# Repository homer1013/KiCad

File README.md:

# KiCad
 PCB projects

 All PCB development saved here

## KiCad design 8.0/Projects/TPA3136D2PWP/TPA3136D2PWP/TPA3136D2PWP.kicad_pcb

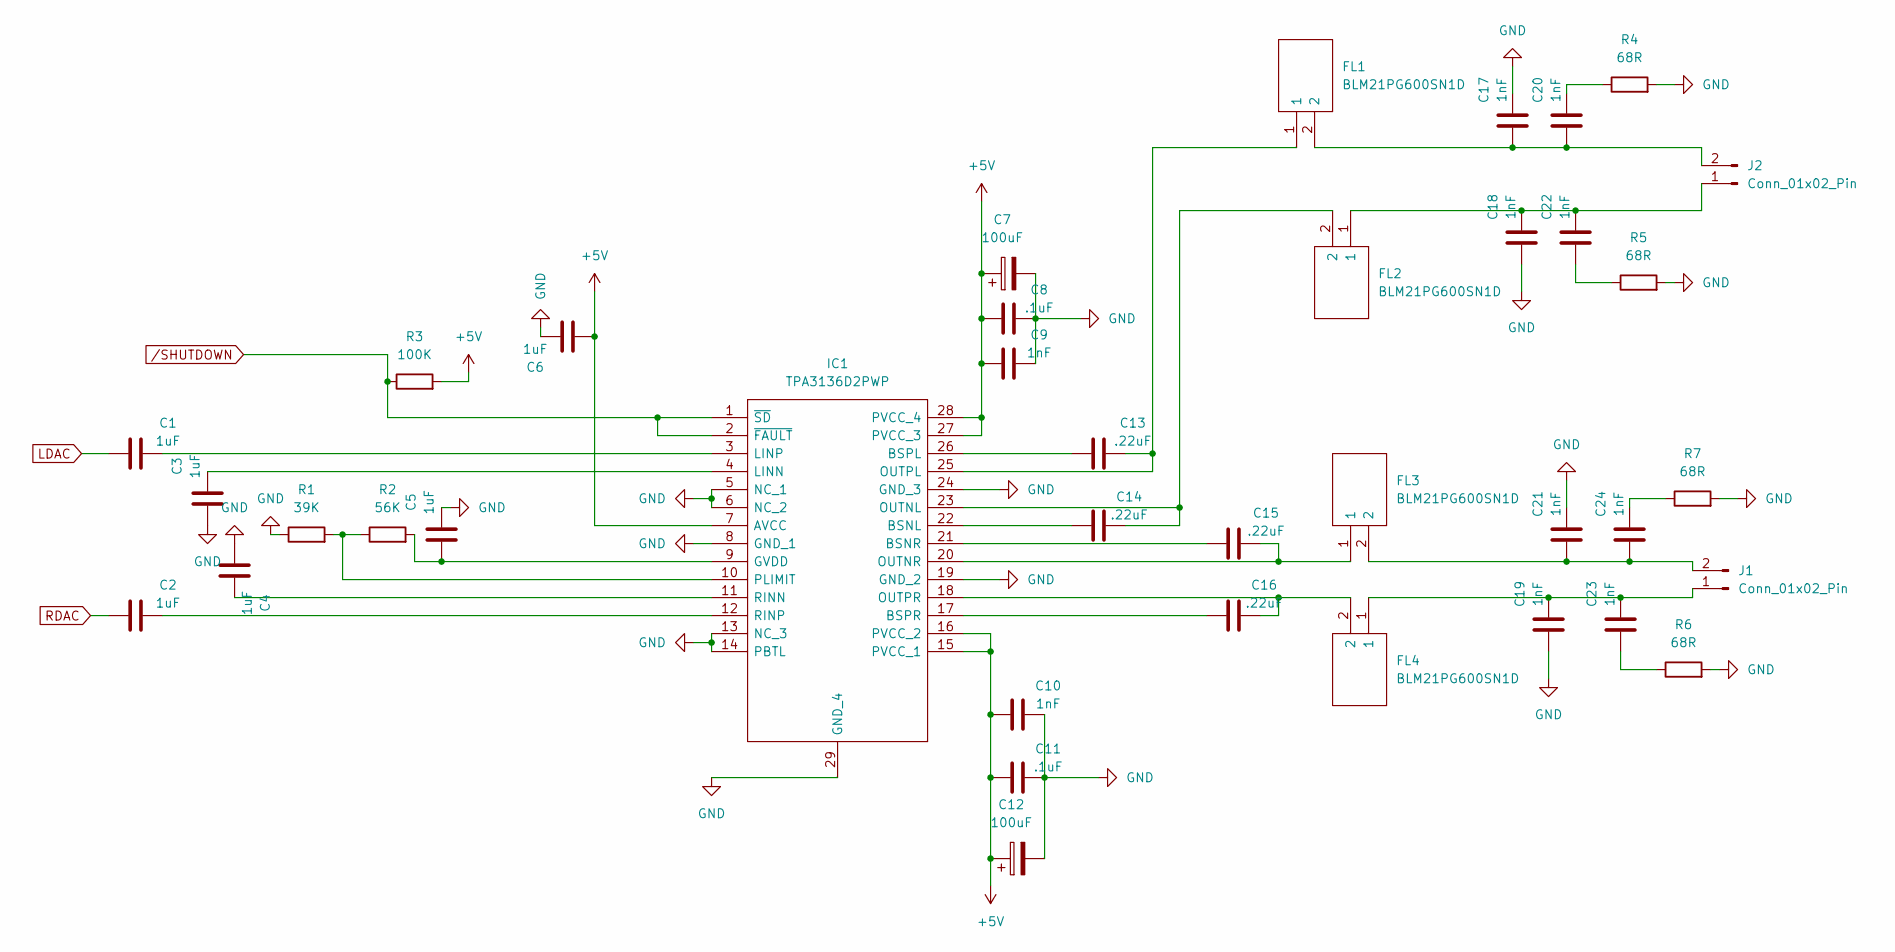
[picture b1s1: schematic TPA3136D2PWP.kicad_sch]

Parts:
C1, C2, C3, C4, C5, C6: 1uF; C_0805_2012Metric_Pad1.18x1.45mm_HandSolder
C7, C12: 100uF; C_0805_2012Metric_Pad1.18x1.45mm_HandSolder
C8, C11: .1uF; C_0805_2012Metric_Pad1.18x1.45mm_HandSolder
C9, C10, C17, C18, C19, C20, C21, C22, C23, C24: 1nF; C_0805_2012Metric_Pad1.18x1.45mm_HandSolder
C13, C14, C15, C16: .22uF; C_0805_2012Metric_Pad1.18x1.45mm_HandSolder
FL1, FL2, FL3, FL4: BLM21PG600SN1D; BLM21AG102BH1J; Mouser Part Number 81-BLM21P600S
IC1: TPA3136D2PWP; SOP65P640X120-29N; Mouser Part Number 595-TPA3136D2PWP
J1, J2: Conn_01x02_Pin; PinHeader_1x02_P2.54mm_Vertical
R1: 39K; R_0805_2012Metric_Pad1.20x1.40mm_HandSolder
R2: 56K; R_0805_2012Metric_Pad1.20x1.40mm_HandSolder
R3: 100K; R_0805_2012Metric_Pad1.20x1.40mm_HandSolder
R4, R5, R6, R7: 68R; R_0805_2012Metric_Pad1.20x1.40mm_HandSolder

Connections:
+5V: C6.2, C7.1, C8.2, C9.2, C10.2, C11.2, C12.1, IC1.7 (AVCC), IC1.15 (PVCC_1), IC1.16 (PVCC_2), IC1.27 (PVCC_3), IC1.28 (PVCC_4), R3.2
GND: C3.2, C4.2, C5.1, C6.1, C7.2, C8.1, C9.1, C10.1, C11.1, C12.2, C17.1, C18.2, C19.2, C21.1, IC1.5 (NC_1), IC1.6 (NC_2), IC1.8 (GND_1), IC1.13 (NC_3), IC1.14 (PBTL), IC1.19 (GND_2), IC1.24 (GND_3), IC1.29 (GND_4), R1.1, R4.2, R5.2, R6.2, R7.2
LDAC: C1.2
unnamed: C20.1, R4.1
unnamed: C22.2, R5.1
unnamed: C23.2, R6.1
unnamed: C24.1, R7.1
unnamed: C14.2, IC1.22 (BSNL)
unnamed: C15.2, IC1.21 (BSNR)
unnamed: C13.2, IC1.26 (BSPL)
unnamed: C16.2, IC1.17 (BSPR)
unnamed: C5.2, IC1.9 (GVDD), R2.2
unnamed: C3.1, IC1.4 (LINN)
unnamed: C1.1, IC1.3 (LINP)
unnamed: C14.1, FL2.2, IC1.23 (OUTNL)
unnamed: C15.1, FL3.1, IC1.20 (OUTNR)
unnamed: C13.1, FL1.1, IC1.25 (OUTPL)
unnamed: C16.1, FL4.2, IC1.18 (OUTPR)
unnamed: IC1.10 (PLIMIT), R1.2, R2.1
unnamed: C4.1, IC1.11 (RINN)
unnamed: C2.1, IC1.12 (RINP)
unnamed: C19.1, C23.1, FL4.1, J1.1
unnamed: C21.2, C24.2, FL3.2, J1.2
unnamed: C18.1, C22.1, FL2.1, J2.1
unnamed: C17.2, C20.2, FL1.2, J2.2
RDAC: C2.2
/SHUTDOWN: IC1.1 (~SD), IC1.2 (~FAULT), R3.1

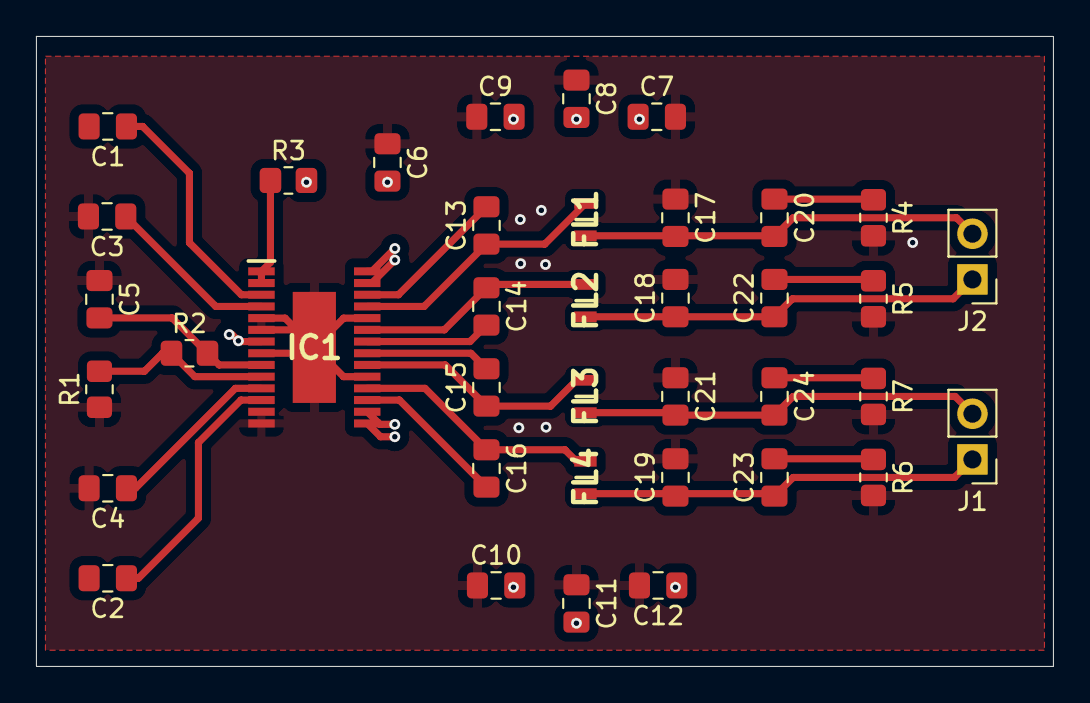
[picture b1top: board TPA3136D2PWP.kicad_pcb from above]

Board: 4 copper layers, 56.5 x 35.0 mm, 38 parts (0 on the bottom side), 25 nets.

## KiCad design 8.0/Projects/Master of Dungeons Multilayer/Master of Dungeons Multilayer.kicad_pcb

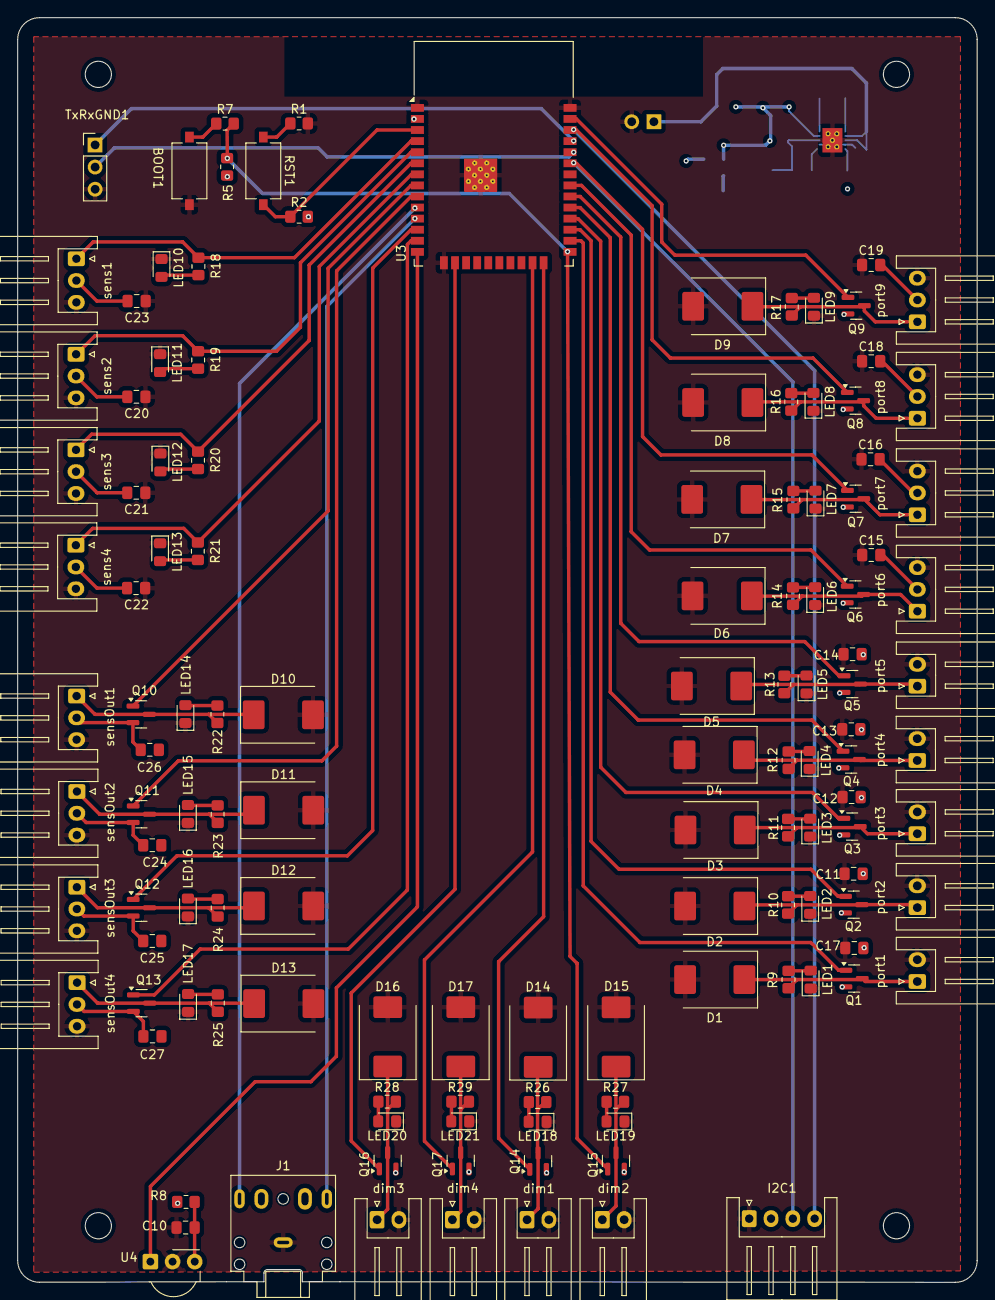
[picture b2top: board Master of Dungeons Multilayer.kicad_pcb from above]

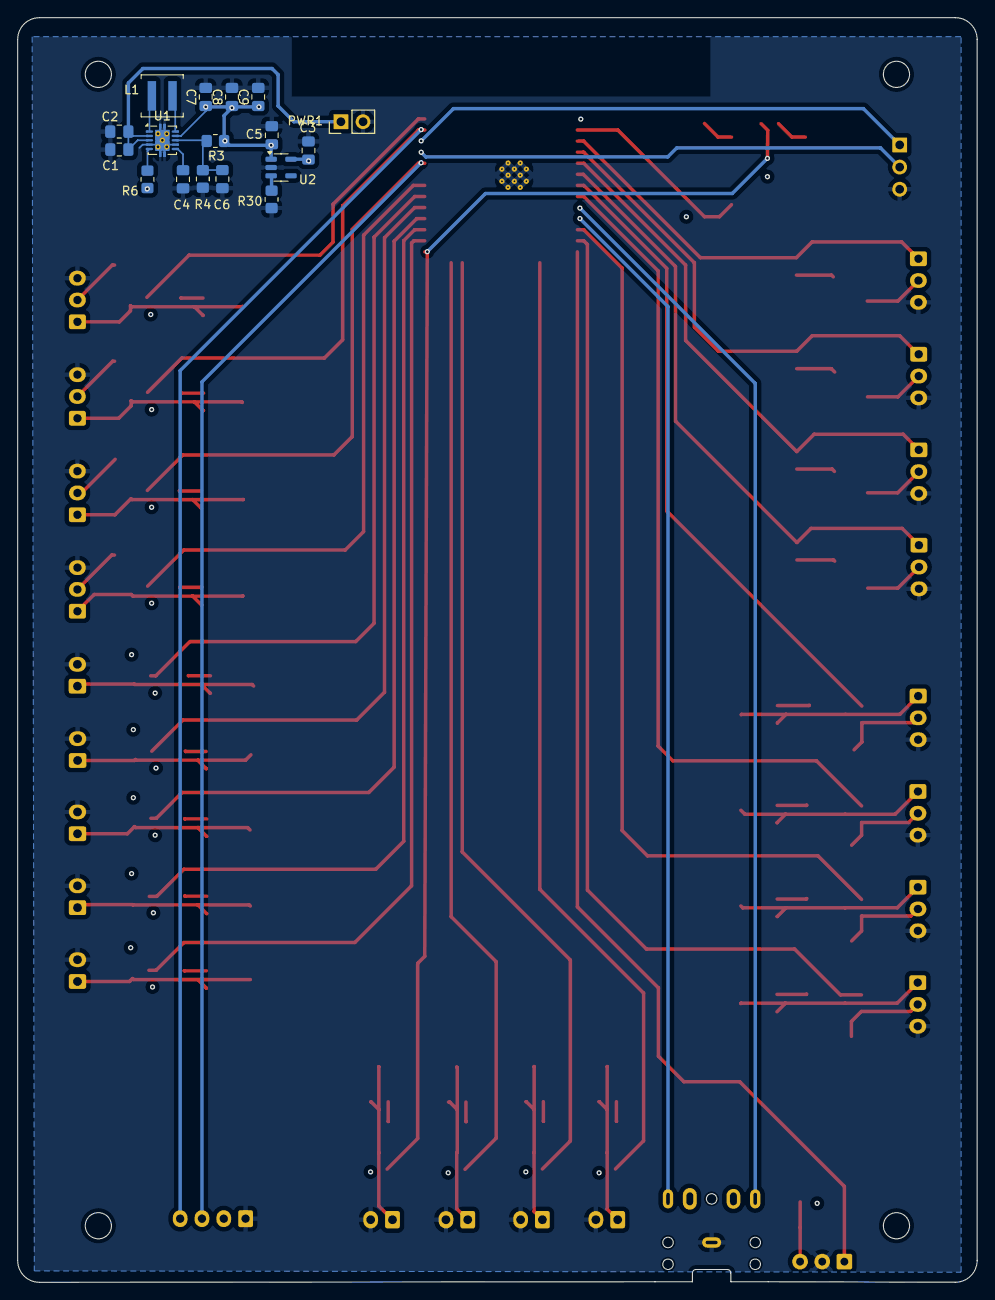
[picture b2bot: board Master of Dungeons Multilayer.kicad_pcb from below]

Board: 4 copper layers, 110.0 x 145.0 mm, 144 parts (17 on the bottom side), 78 nets.

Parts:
BOOT1: SW_Push; SW_Tactile_SPST_NO_Straight_CK_PTS636Sx25SMTRLFS
C1, C2: 10uF; C_0805_2012Metric_Pad1.18x1.45mm_HandSolder
C3, C5: 1uF; C_0805_2012Metric_Pad1.18x1.45mm_HandSolder
C4: .1uF; C_0805_2012Metric_Pad1.18x1.45mm_HandSolder
C6: 10pF; C_0805_2012Metric_Pad1.18x1.45mm_HandSolder
C7, C8, C9: 22uF; C_0805_2012Metric_Pad1.18x1.45mm_HandSolder
C10, C11, C12, C13, C14, C15, C16, C17, C18, C19: 100nF; C_0805_2012Metric_Pad1.18x1.45mm_HandSolder
C20, C21, C22, C23, C24, C25, C26, C27: C; C_0805_2012Metric_Pad1.18x1.45mm_HandSolder
D1, D2, D3, D4, D5, D6, D7, D8, D9, D10, D11, D12, D13, D14, D15, D16, D17: B340; D_SMC
I2C1: Conn_01x04_Pin; JST_XH_S4B-XH-A_1x04_P2.50mm_Horizontal
J1: AudioPlug3; Jack_3.5mm_CUI_SJ1-3525N_Horizontal
L1: L; L_Coilcraft_XAL4020-XXX
LED1, LED2, LED3, LED4, LED5, LED6, LED7, LED8, LED9, LED10, LED11, LED12, LED13: GREEN_0805; LED_0805_2012Metric_Pad1.15x1.40mm_HandSolder
LED14, LED15, LED16, LED17, LED18, LED19, LED20, LED21: LED; LED_0805_2012Metric_Pad1.15x1.40mm_HandSolder
PWR1: Conn_01x02_Pin; PinHeader_1x02_P2.54mm_Vertical
Q1, Q2, Q3, Q4, Q5, Q6, Q7, Q8, Q9, Q10, Q11, Q12, Q13, Q14, Q15, Q16, Q17: IRLML6244; SOT-23
R1, R7, R8: 470R; R_0805_2012Metric_Pad1.20x1.40mm_HandSolder
R2, R5, R9, R10, R11, R12, R13, R14, R15, R16, R17, R30: 12K; R_0805_2012Metric_Pad1.20x1.40mm_HandSolder
R3, R6: 1M; R_0805_2012Metric_Pad1.20x1.40mm_HandSolder
R4: 111K; R_0805_2012Metric_Pad1.20x1.40mm_HandSolder
R18, R19, R20, R21, R22, R23, R24, R25, R26, R27, R28, R29: R; R_0805_2012Metric_Pad1.20x1.40mm_HandSolder
RST1: SW_Push; SW_Tactile_SPST_NO_Straight_CK_PTS636Sx25SMTRLFS
TxRxGND1: Conn_01x03_Pin; PinHeader_1x03_P2.54mm_Vertical
U1: TPS63060; Texas_DSC0010J_ThermalVias
U2: AP2127K-3.3; SOT-23-5
U3: ESP32-WROOM-32E; ESP32-WROOM-32D
U4: TSOP45xx; Vishay_MOLD-3Pin
dim1, dim2, dim3, dim4: Conn_01x02_Pin; JST_XH_S2B-XH-A_1x02_P2.50mm_Horizontal
port1, port2, port3, port4, port5: JST_XH_2POS; JST_XH_S2B-XH-A_1x02_P2.50mm_Horizontal
port6, port7, port8, port9: JST_XH_3POS; JST_XH_S3B-XH-A_1x03_P2.50mm_Horizontal
sens1, sens2, sens3, sens4: Conn_01x03_Pin; JST_XH_S3B-XH-A_1x03_P2.50mm_Horizontal
sensOut1, sensOut2, sensOut3, sensOut4: Conn_01x03_Pin; JST_XH_S3B-XH-A_1x03_P2.50mm_Horizontal

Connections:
+3.3V: C3.1, R2.2, R5.1, U2.5 (VOUT), U3.2 (VDD)
+5V: C5.1, C7.1, C8.1, C9.1, C11.2, C12.2, C13.2, C14.2, C15.2, C16.2, C17.2, C18.2, C19.2, C20.1, C21.1, C22.1, C23.1, C24.2, C25.2, C26.2, C27.2, I2C1.2, Q1.2 (S), Q2.2 (S), Q3.2 (S), Q4.2 (S), Q5.2 (S), Q6.2 (S), Q7.2 (S), Q8.2 (S), Q9.2 (S), Q10.2 (S), Q11.2 (S), Q12.2 (S), Q13.2 (S), Q14.2 (S), Q15.2 (S), Q16.2 (S), Q17.2 (S), R3.2, R6.2, R8.2, U1.9 (VOUT), U2.1 (VIN), port6.2, port7.2, port8.2, port9.2, sens1.2, sens2.2, sens3.2, sens4.2, sensOut1.2, sensOut2.2, sensOut3.2, sensOut4.2
GND: BOOT1.2, C1.1, C2.2, C3.2, C4.2, C5.2, C6.2, C7.2, C8.2, C9.2, C10.1, C11.1, C12.1, C13.1, C14.1, C15.1, C16.1, C17.1, C18.1, C19.1, C20.2, C21.2, C22.2, C23.2, D1.2 (A), D2.2 (A), D3.2 (A), D4.2 (A), D5.2 (A), D6.2 (A), D7.2 (A), D8.2 (A), D9.2 (A), D10.2 (A), D11.2 (A), D12.2 (A), D13.2 (A), D14.2 (A), D15.2 (A), D16.2 (A), D17.2 (A), I2C1.1, J1.S, LED1.1 (K), LED2.1 (K), LED3.1 (K), LED4.1 (K), LED5.1 (K), LED6.1 (K), LED7.1 (K), LED8.1 (K), LED9.1 (K), LED10.1 (K), LED11.1 (K), LED12.1 (K), LED13.1 (K), LED14.1 (K), LED15.1 (K), LED16.1 (K), LED17.1 (K), LED18.1 (K), LED19.1 (K), LED20.1 (K), LED21.1 (K), PWR1.2, R1.2, R4.1, R30.1, TxRxGND1.3, U1.4 (PS/SYNC), U1.7 (GND), U1.11 (PGND), U2.2 (GND), U3.1 (GND), U3.15 (GND), U3.38 (GND), U3.39 (GND), U4.2 (GND), dim1.2, dim2.2, dim3.2, dim4.2, port1.2, port2.2, port3.2, port4.2, port5.2, port6.3, port7.3, port8.3, port9.3, sens1.3, sens2.3, sens3.3, sens4.3, sensOut1.3, sensOut2.3, sensOut3.3, sensOut4.3
unnamed: BOOT1.1, R7.1
unnamed: D1.1 (K), Q1.3 (D), R9.1, port1.1
unnamed: D2.1 (K), Q2.3 (D), R10.1, port2.1
unnamed: D3.1 (K), Q3.3 (D), R11.1, port3.1
unnamed: D4.1 (K), Q4.3 (D), R12.1, port4.1
unnamed: D5.1 (K), Q5.3 (D), R13.1, port5.1
unnamed: D6.1 (K), Q6.3 (D), R14.1, port6.1
unnamed: D7.1 (K), Q7.3 (D), R15.1, port7.1
unnamed: D8.1 (K), Q8.3 (D), R16.1, port8.1
unnamed: D9.1 (K), Q9.3 (D), R17.1, port9.1
unnamed: D10.1 (K), Q10.3 (D), R22.2, sensOut1.1
unnamed: D11.1 (K), Q11.3 (D), R23.2, sensOut2.1
unnamed: D12.1 (K), Q12.3 (D), R24.2, sensOut3.1
unnamed: D13.1 (K), Q13.3 (D), R25.2, sensOut4.1
unnamed: D14.1 (K), Q14.3 (D), R26.2, dim1.1
unnamed: D15.1 (K), Q15.3 (D), R27.2, dim2.1
unnamed: D16.1 (K), Q16.3 (D), R28.2, dim3.1
unnamed: D17.1 (K), Q17.3 (D), R29.2, dim4.1
unnamed: LED1.2 (A), R9.2
unnamed: LED2.2 (A), R10.2
unnamed: LED3.2 (A), R11.2
unnamed: LED4.2 (A), R12.2
unnamed: LED5.2 (A), R13.2
unnamed: LED6.2 (A), R14.2
unnamed: LED7.2 (A), R15.2
unnamed: LED8.2 (A), R16.2
unnamed: LED9.2 (A), R17.2
unnamed: LED10.2 (A), R18.1
unnamed: LED11.2 (A), R19.1
unnamed: LED12.2 (A), R20.1
unnamed: LED13.2 (A), R21.1
unnamed: LED14.2 (A), R22.1
unnamed: LED15.2 (A), R23.1
unnamed: LED16.2 (A), R24.1
unnamed: LED17.2 (A), R25.1
unnamed: LED18.2 (A), R26.1
unnamed: LED19.2 (A), R27.1
unnamed: LED20.2 (A), R28.1
unnamed: LED21.2 (A), R29.1
unnamed: C1.2, C2.1, PWR1.1, U1.2 (VIN), U1.3 (EN)
unnamed: R1.1, RST1.1
unnamed: TxRxGND1.1, U3.35 (TXD0/IO1)
unnamed: TxRxGND1.2, U3.34 (RXD0/IO3)
unnamed: C6.1, R3.1, R4.2, U1.8 (FB)
unnamed: L1.2, U1.1 (L1)
unnamed: L1.1, U1.10 (L2)
unnamed: R6.1, U1.5 (PG)
unnamed: C4.1, U1.6 (VAUX)
unnamed: R30.2, U2.3 (EN)
unnamed: R2.1, RST1.2, U3.3 (EN)
unnamed: U3.14 (IO12), U4.1 (OUT)
unnamed: J1.R, U3.10 (IO25)
unnamed: J1.T, U3.11 (IO26)
unnamed: C10.2, R8.1, U4.3 (Vs)
dim1: Q16.1 (G), U3.16 (IO13)
dim2: Q17.1 (G), U3.23 (IO15)
dim3: Q14.1 (G), U3.24 (IO2)
dim4: Q15.1 (G), R5.2, R7.2, U3.25 (IO0)
port1: Q1.1 (G), U3.26 (IO4)
port2: Q2.1 (G), U3.27 (IO16)
port3: Q3.1 (G), U3.28 (IO17)
port4: Q4.1 (G), U3.29 (IO5)
port5: Q5.1 (G), U3.30 (IO18)
port6: Q6.1 (G), U3.31 (IO19)
port7: I2C1.3, Q7.1 (G), U3.33 (IO21)
port8: I2C1.4, Q8.1 (G), U3.36 (IO22)
port9: Q9.1 (G), U3.37 (IO23)
sens1: R18.2, U3.4 (SENSOR_VP), sens1.1
sens2: R19.2, U3.5 (SENSOR_VN), sens2.1
sens3: R20.2, U3.6 (IO34), sens3.1
sens4: R21.2, U3.7 (IO35), sens4.1
sensOut1: Q10.1 (G), U3.8 (IO32)
sensOut2: Q11.1 (G), U3.9 (IO33)
sensOut3: Q12.1 (G), U3.12 (IO27)
sensOut4: Q13.1 (G), U3.13 (IO14)

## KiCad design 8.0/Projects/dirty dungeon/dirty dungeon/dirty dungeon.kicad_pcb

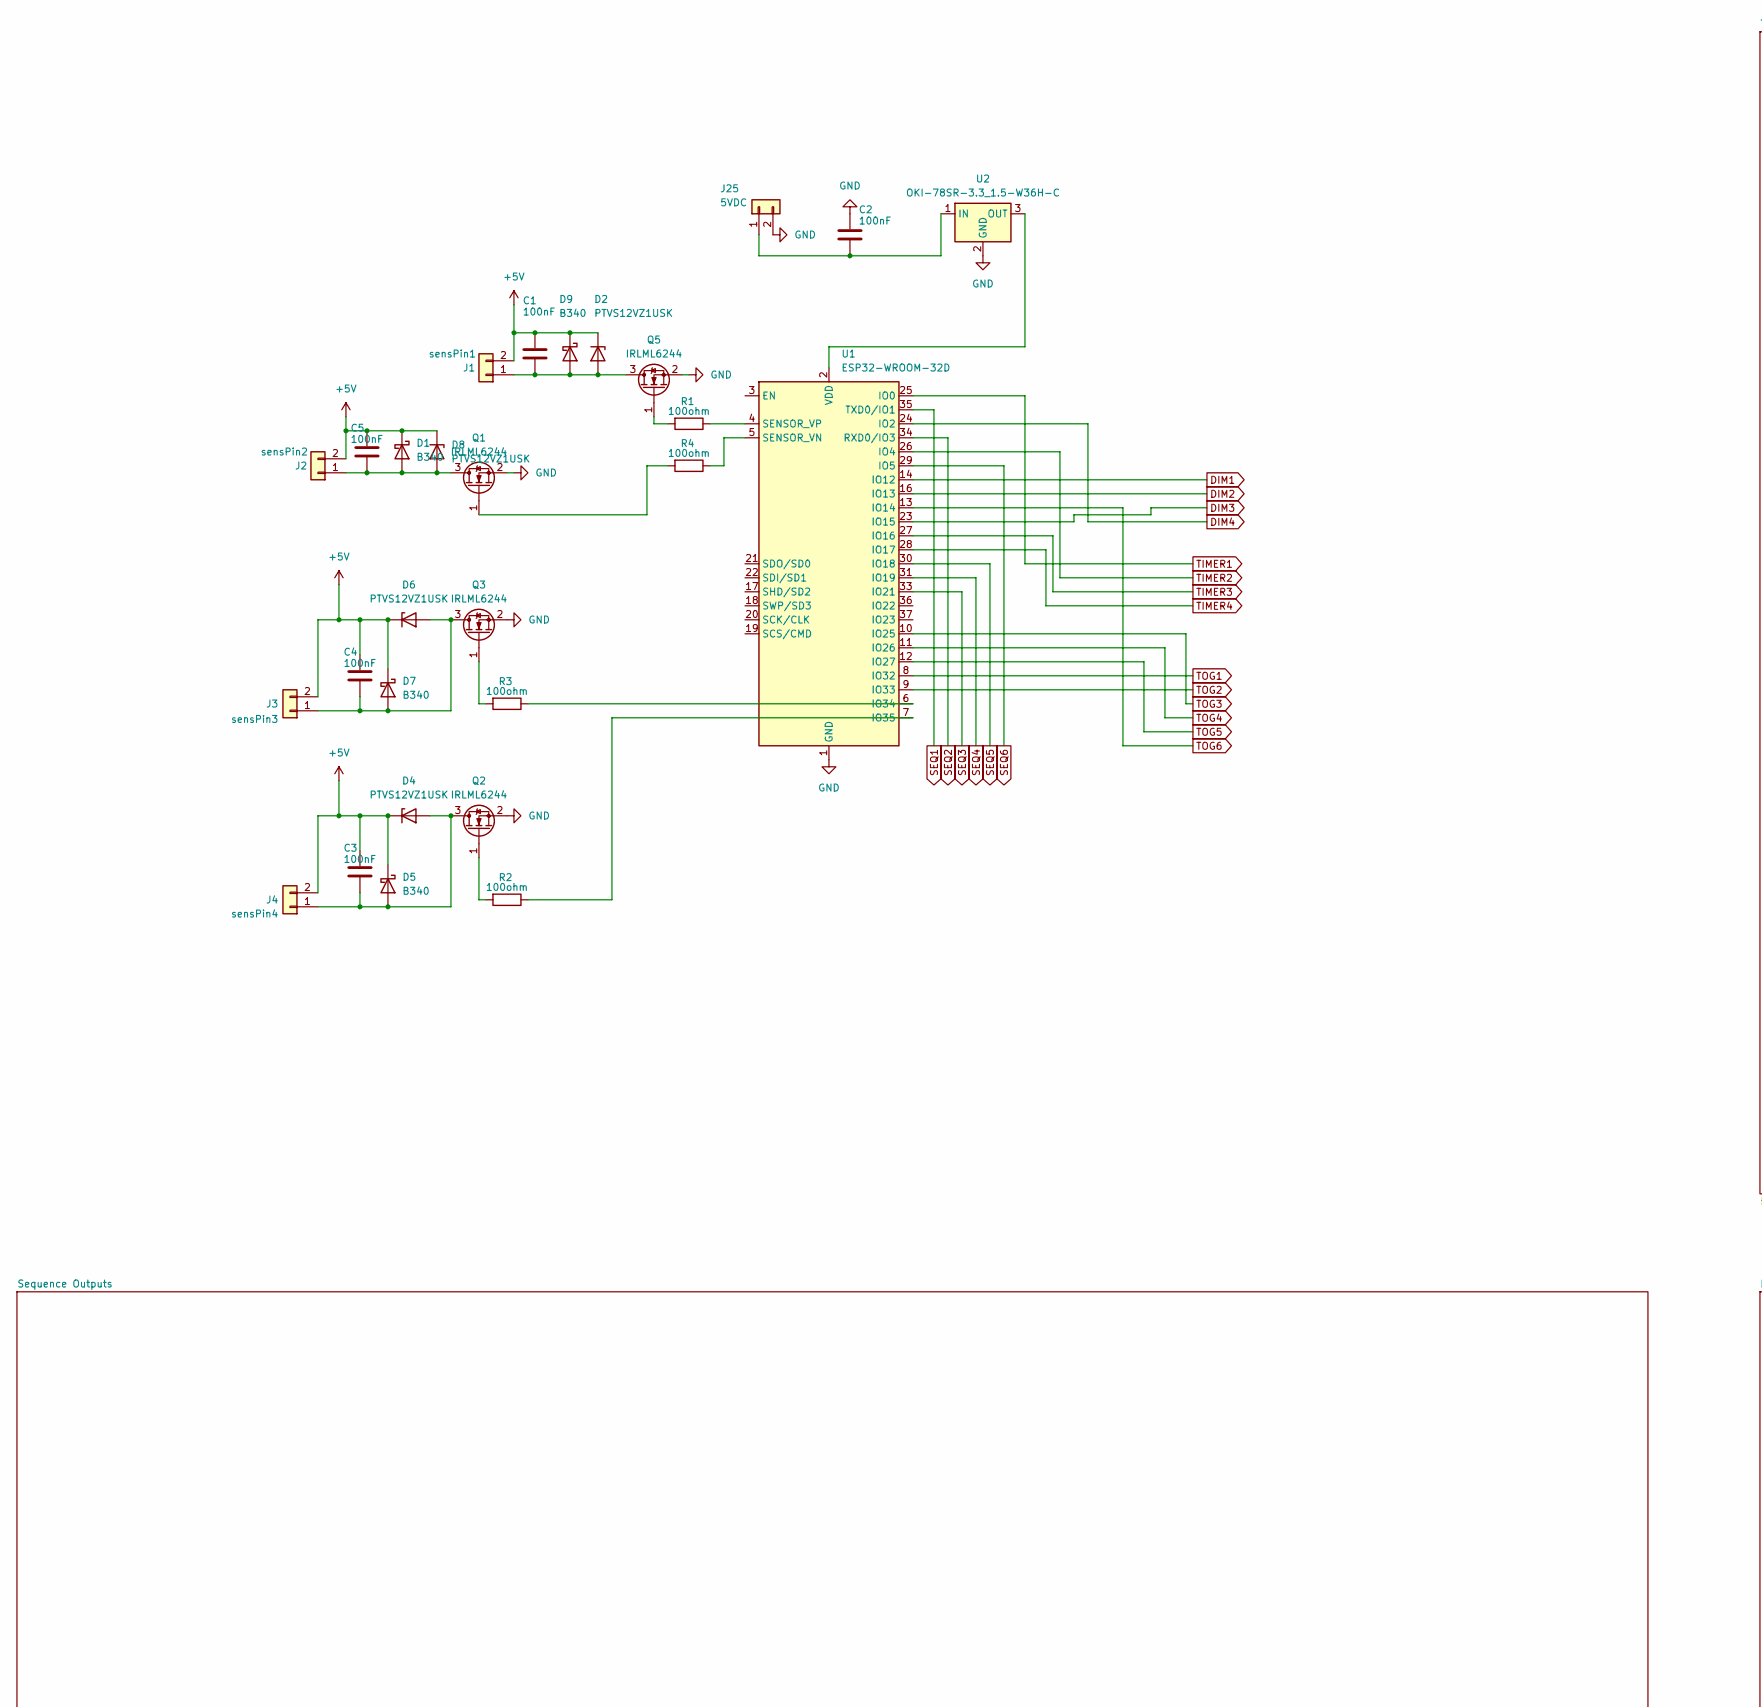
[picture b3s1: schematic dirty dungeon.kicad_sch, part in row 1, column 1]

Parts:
C1, C2, C3, C4, C5: 100nF; C_0603_1608Metric_Pad1.08x0.95mm_HandSolder
D1, D5, D7, D9: B340; D_SMC
D2, D4, D6, D8: PTVS12VZ1USK; Nexperia_DSN1608-2_1.6x0.8mm
J1: sensPin1; JST_XH_S2B-XH-A_1x02_P2.50mm_Horizontal
J2: sensPin2; JST_XH_S2B-XH-A_1x02_P2.50mm_Horizontal
J3: sensPin3; JST_XH_S2B-XH-A_1x02_P2.50mm_Horizontal
J4: sensPin4; JST_XH_S2B-XH-A_1x02_P2.50mm_Horizontal
J25: 5VDC; JST_XH_S2B-XH-A_1x02_P2.50mm_Horizontal
Q1, Q2, Q3, Q5: IRLML6244; SOT-23
R1, R2, R3, R4: 100ohm; R_0603_1608Metric_Pad0.98x0.95mm_HandSolder
U1: ESP32-WROOM-32D
U2: OKI-78SR-3.3_1.5-W36H-C; Converter_DCDC_Murata_OKI-78SR_Horizontal

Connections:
+5V: C1.1, C3.1, C4.1, C5.1, D1.1 (K), D2.1 (K), D4.1 (K), D5.1 (K), D6.1 (K), D7.1 (K), D8.1 (K), D9.1 (K), J1.2, J2.2, J3.2, J4.2; also elsewhere on the board
DIM1: U1.14 (IO12)
DIM2: U1.16 (IO13)
DIM3: U1.23 (IO15)
DIM4: U1.24 (IO2)
GND: C2.1, J25.2, Q1.2 (S), Q2.2 (S), Q3.2 (S), Q5.2 (S), U1.1 (GND), U1.15 (GND), U1.38 (GND), U1.39 (GND), U2.2 (GND); also elsewhere on the board
unnamed: C5.2, D1.2 (A), D8.2 (A), J2.1, Q1.3 (D)
unnamed: C1.2, D2.2 (A), D9.2 (A), J1.1, Q5.3 (D)
unnamed: C3.2, D4.2 (A), D5.2 (A), J4.1, Q2.3 (D)
unnamed: C4.2, D6.2 (A), D7.2 (A), J3.1, Q3.3 (D)
unnamed: C2.2, J25.1, U2.1 (IN)
unnamed: Q1.1 (G), R4.2
unnamed: Q2.1 (G), R2.2
unnamed: Q3.1 (G), R3.2
unnamed: Q5.1 (G), R1.2
unnamed: R3.1, U1.6 (IO34)
unnamed: R2.1, U1.7 (IO35)
unnamed: R4.1, U1.5 (SENSOR_VN)
unnamed: R1.1, U1.4 (SENSOR_VP)
unnamed: U1.2 (VDD), U2.3 (OUT)
SEQ1: U1.35 (TXD0/IO1)
SEQ2: U1.34 (RXD0/IO3)
SEQ3: U1.33 (IO21)
SEQ4: U1.31 (IO19)
SEQ5: U1.30 (IO18)
SEQ6: U1.29 (IO5)
TIMER1: U1.25 (IO0)
TIMER2: U1.26 (IO4)
TIMER3: U1.27 (IO16)
TIMER4: U1.28 (IO17)
TOG1: U1.8 (IO32)
TOG2: U1.9 (IO33)
TOG3: U1.10 (IO25)
TOG4: U1.11 (IO26)
TOG5: U1.12 (IO27)
TOG6: U1.13 (IO14)

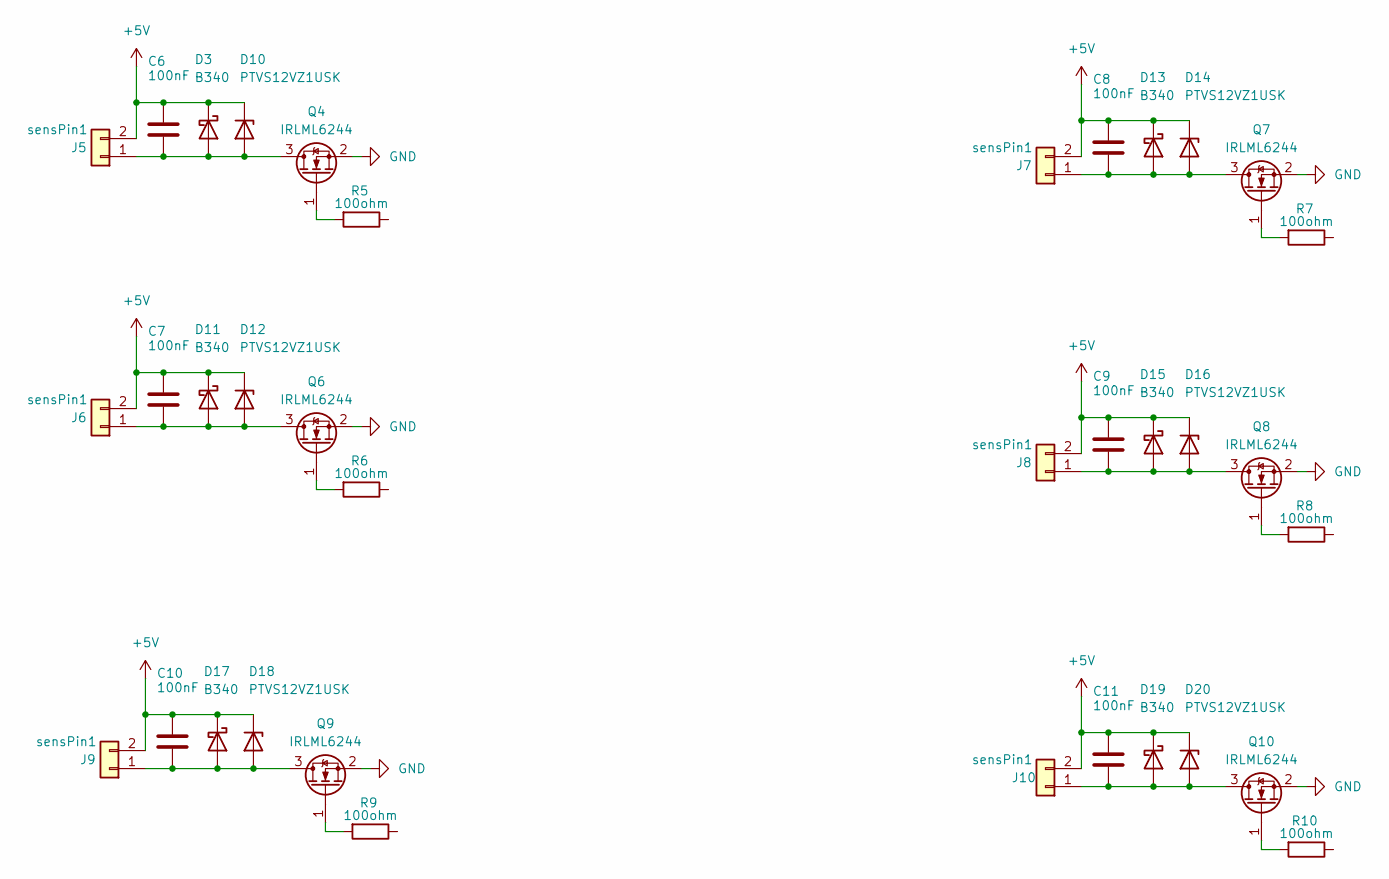
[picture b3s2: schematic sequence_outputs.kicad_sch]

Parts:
C6, C7, C8, C9, C10, C11: 100nF; C_0603_1608Metric_Pad1.08x0.95mm_HandSolder
D3, D11, D13, D15, D17, D19: B340; D_SMC
D10, D12, D14, D16, D18, D20: PTVS12VZ1USK; Nexperia_DSN1608-2_1.6x0.8mm
J5, J6, J7, J8, J9, J10: sensPin1; JST_XH_S2B-XH-A_1x02_P2.50mm_Horizontal
Q4, Q6, Q7, Q8, Q9, Q10: IRLML6244; SOT-23
R5, R6, R7, R8, R9, R10: 100ohm; R_0603_1608Metric_Pad0.98x0.95mm_HandSolder

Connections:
+5V: C6.1, C7.1, C8.1, C9.1, C10.1, C11.1, D3.1 (K), D10.1 (K), D11.1 (K), D12.1 (K), D13.1 (K), D14.1 (K), D15.1 (K), D16.1 (K), D17.1 (K), D18.1 (K), D19.1 (K), D20.1 (K), J5.2, J6.2, J7.2, J8.2, J9.2, J10.2; also elsewhere on the board
GND: Q4.2 (S), Q6.2 (S), Q7.2 (S), Q8.2 (S), Q9.2 (S), Q10.2 (S); also elsewhere on the board
unnamed: C6.2, D3.2 (A), D10.2 (A), J5.1, Q4.3 (D)
unnamed: C7.2, D11.2 (A), D12.2 (A), J6.1, Q6.3 (D)
unnamed: C8.2, D13.2 (A), D14.2 (A), J7.1, Q7.3 (D)
unnamed 13: C9.2, D15.2 (A), D16.2 (A), J8.1, Q8.3 (D); also elsewhere on the board
unnamed: C10.2, D17.2 (A), D18.2 (A), J9.1, Q9.3 (D)
unnamed: C11.2, D19.2 (A), D20.2 (A), J10.1, Q10.3 (D)
unnamed: Q4.1 (G), R5.2
unnamed: Q6.1 (G), R6.2
unnamed: Q7.1 (G), R7.2
unnamed: Q8.1 (G), R8.2
unnamed: Q9.1 (G), R9.2
unnamed: Q10.1 (G), R10.2

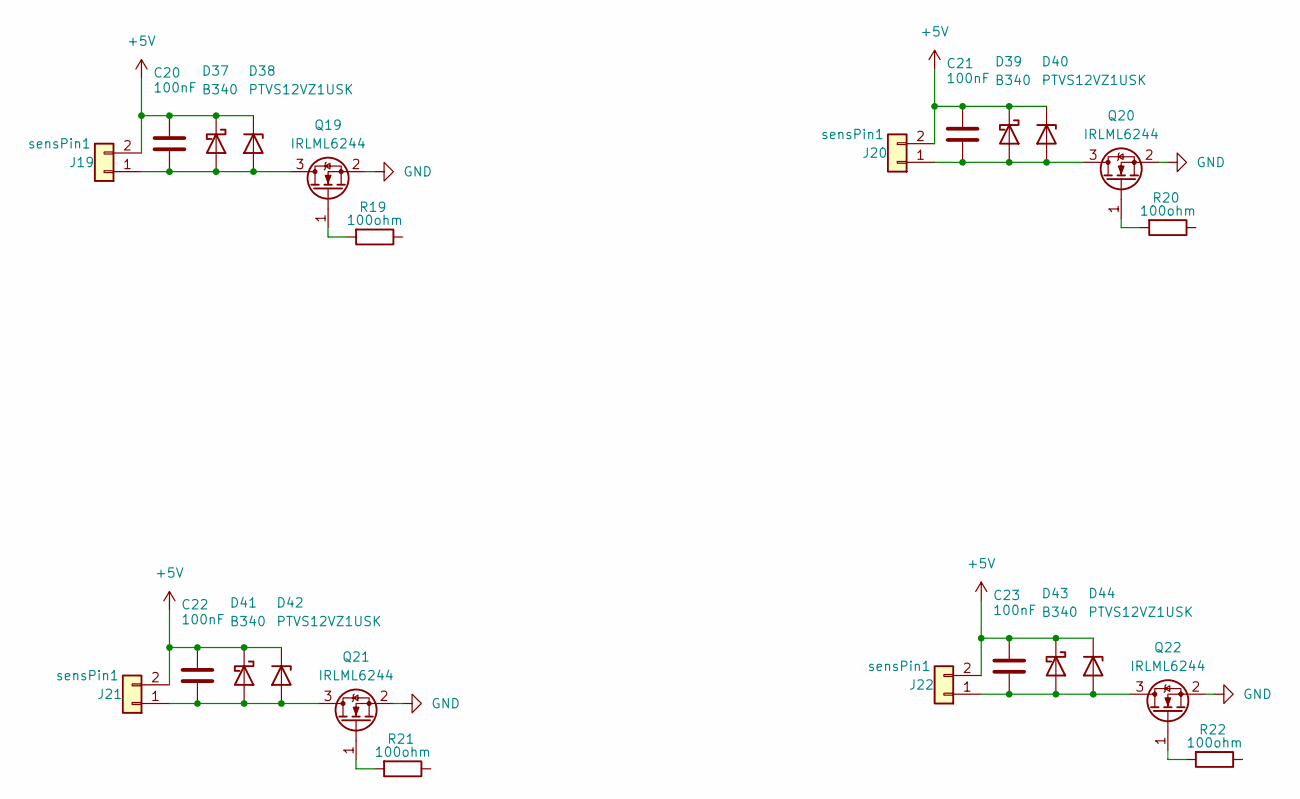
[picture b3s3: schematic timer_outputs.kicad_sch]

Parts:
C20, C21, C22, C23: 100nF; C_0603_1608Metric_Pad1.08x0.95mm_HandSolder
D37, D39, D41, D43: B340; D_SMC
D38, D40, D42, D44: PTVS12VZ1USK; Nexperia_DSN1608-2_1.6x0.8mm
J19, J20, J21, J22: sensPin1; JST_XH_S2B-XH-A_1x02_P2.50mm_Horizontal
Q19, Q20, Q21, Q22: IRLML6244; SOT-23
R19, R20, R21, R22: 100ohm; R_0603_1608Metric_Pad0.98x0.95mm_HandSolder

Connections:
+5V: C20.1, C21.1, C22.1, C23.1, D37.1 (K), D38.1 (K), D39.1 (K), D40.1 (K), D41.1 (K), D42.1 (K), D43.1 (K), D44.1 (K), J19.2, J20.2, J21.2, J22.2; also elsewhere on the board
GND: Q19.2 (S), Q20.2 (S), Q21.2 (S), Q22.2 (S); also elsewhere on the board
unnamed 24: C20.2, D37.2 (A), D38.2 (A), J19.1, Q19.3 (D); also elsewhere on the board
unnamed: C21.2, D39.2 (A), D40.2 (A), J20.1, Q20.3 (D)
unnamed: C22.2, D41.2 (A), D42.2 (A), J21.1, Q21.3 (D)
unnamed: C23.2, D43.2 (A), D44.2 (A), J22.1, Q22.3 (D)
unnamed: Q19.1 (G), R19.2
unnamed: Q20.1 (G), R20.2
unnamed: Q21.1 (G), R21.2
unnamed: Q22.1 (G), R22.2

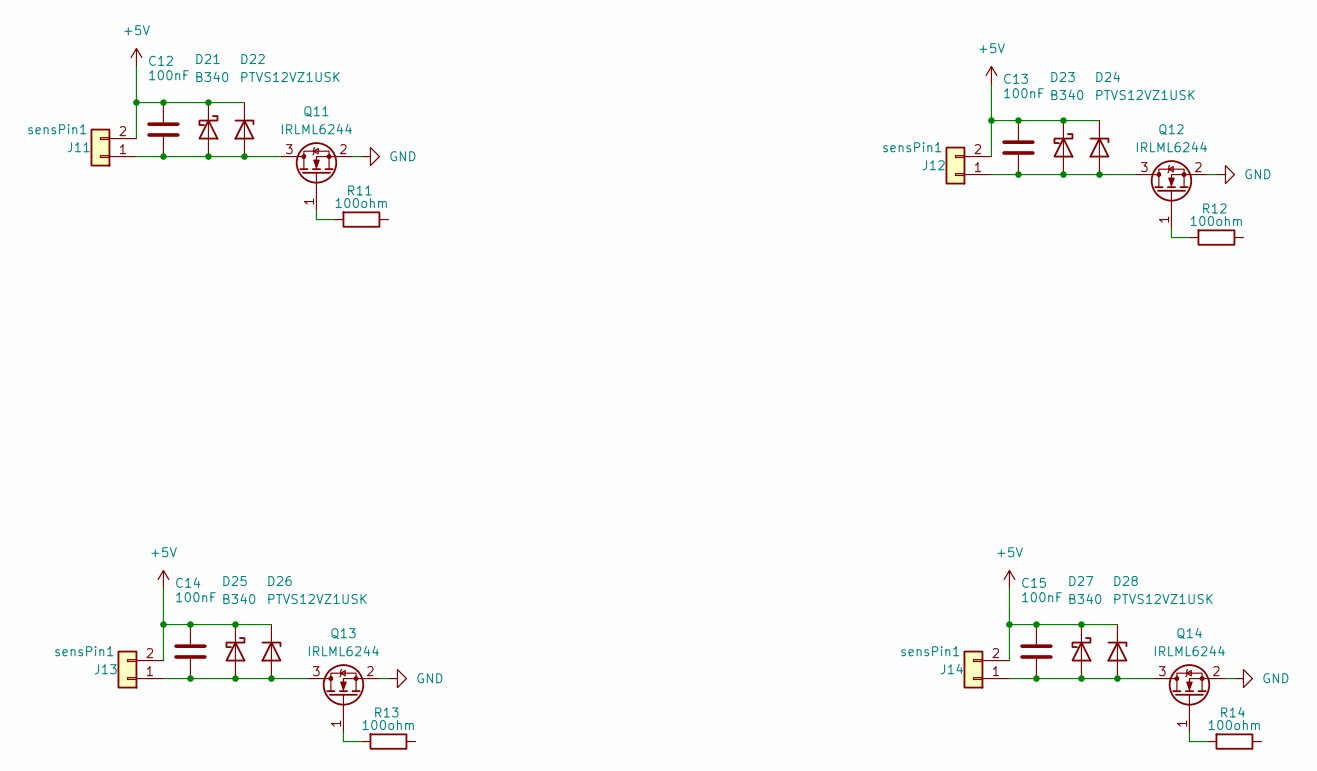
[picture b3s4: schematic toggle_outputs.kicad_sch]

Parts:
C12, C13, C14, C15: 100nF; C_0603_1608Metric_Pad1.08x0.95mm_HandSolder
D21, D23, D25, D27: B340; D_SMC
D22, D24, D26, D28: PTVS12VZ1USK; Nexperia_DSN1608-2_1.6x0.8mm
J11, J12, J13, J14: sensPin1; JST_XH_S2B-XH-A_1x02_P2.50mm_Horizontal
Q11, Q12, Q13, Q14: IRLML6244; SOT-23
R11, R12, R13, R14: 100ohm; R_0603_1608Metric_Pad0.98x0.95mm_HandSolder

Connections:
+5V: C12.1, C13.1, C14.1, C15.1, D21.1 (K), D22.1 (K), D23.1 (K), D24.1 (K), D25.1 (K), D26.1 (K), D27.1 (K), D28.1 (K), J11.2, J12.2, J13.2, J14.2; also elsewhere on the board
GND: Q11.2 (S), Q12.2 (S), Q13.2 (S), Q14.2 (S); also elsewhere on the board
unnamed: C12.2, D21.2 (A), D22.2 (A), J11.1, Q11.3 (D)
unnamed: C13.2, D23.2 (A), D24.2 (A), J12.1, Q12.3 (D)
unnamed: C14.2, D25.2 (A), D26.2 (A), J13.1, Q13.3 (D)
unnamed: C15.2, D27.2 (A), D28.2 (A), J14.1, Q14.3 (D)
unnamed: Q11.1 (G), R11.2
unnamed: Q12.1 (G), R12.2
unnamed: Q13.1 (G), R13.2
unnamed: Q14.1 (G), R14.2

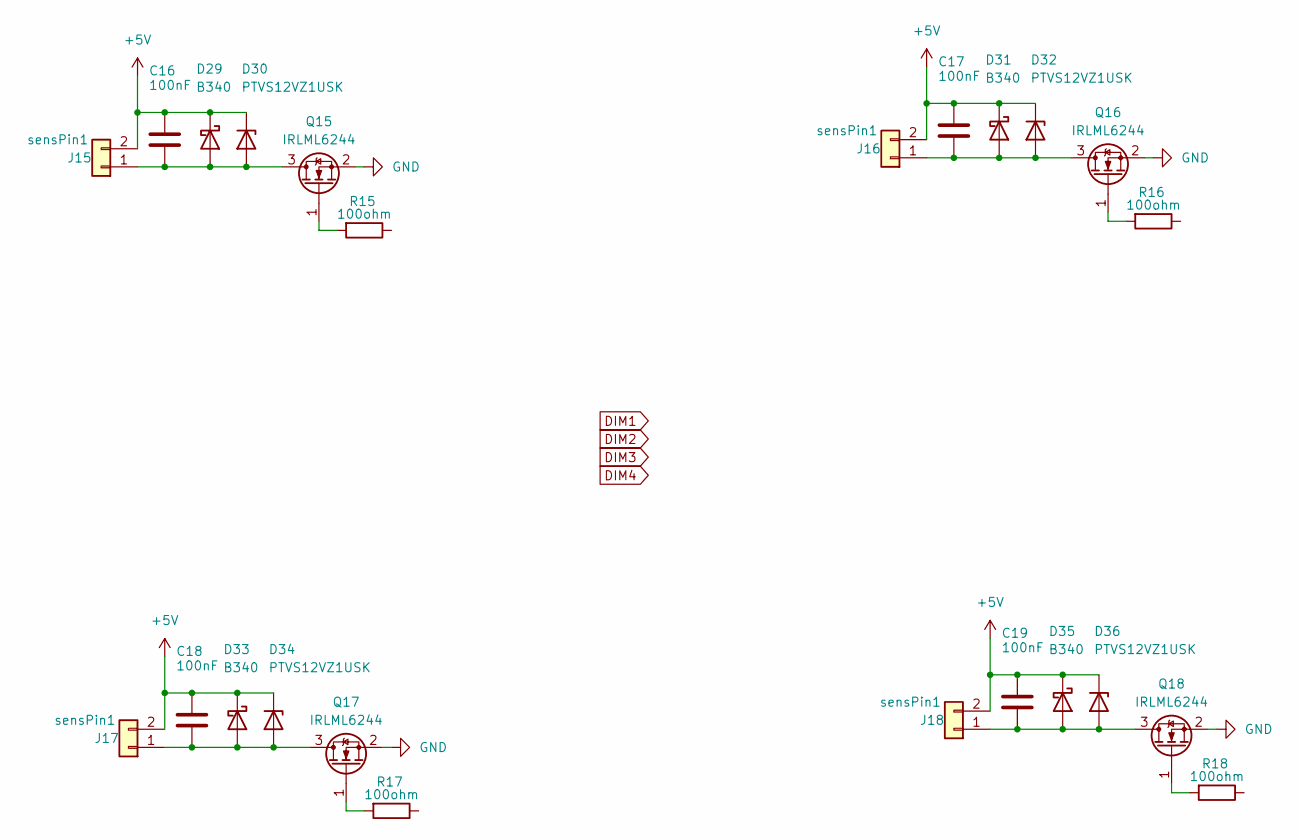
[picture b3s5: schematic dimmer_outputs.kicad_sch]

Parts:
C16, C17, C18, C19: 100nF; C_0603_1608Metric_Pad1.08x0.95mm_HandSolder
D29, D31, D33, D35: B340; D_SMC
D30, D32, D34, D36: PTVS12VZ1USK; Nexperia_DSN1608-2_1.6x0.8mm
J15, J16, J17, J18: sensPin1; JST_XH_S2B-XH-A_1x02_P2.50mm_Horizontal
Q15, Q16, Q17, Q18: IRLML6244; SOT-23
R15, R16, R17, R18: 100ohm; R_0603_1608Metric_Pad0.98x0.95mm_HandSolder

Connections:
+5V: C16.1, C17.1, C18.1, C19.1, D29.1 (K), D30.1 (K), D31.1 (K), D32.1 (K), D33.1 (K), D34.1 (K), D35.1 (K), D36.1 (K), J15.2, J16.2, J17.2, J18.2; also elsewhere on the board
GND: Q15.2 (S), Q16.2 (S), Q17.2 (S), Q18.2 (S); also elsewhere on the board
unnamed: C16.2, D29.2 (A), D30.2 (A), J15.1, Q15.3 (D)
unnamed: C17.2, D31.2 (A), D32.2 (A), J16.1, Q16.3 (D)
unnamed: C18.2, D33.2 (A), D34.2 (A), J17.1, Q17.3 (D)
unnamed: C19.2, D35.2 (A), D36.2 (A), J18.1, Q18.3 (D)
unnamed: Q15.1 (G), R15.2
unnamed: Q16.1 (G), R16.2
unnamed: Q17.1 (G), R17.2
unnamed: Q18.1 (G), R18.2

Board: 2 copper layers, 138 parts (0 on the bottom side), 52 nets, no tracks yet.

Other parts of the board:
J8#2, J19#2: sensPin1; JST_XH_S2B-XH-A_1x02_P2.50mm_Horizontal

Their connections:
+5V: J8#2.2, J19#2.2; also elsewhere on the board
unnamed 13: J8#2.1; also elsewhere on the board
unnamed 24: J19#2.1; also elsewhere on the board
